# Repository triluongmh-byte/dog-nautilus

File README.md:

# Nautilus Dog V0

A phone-controlled, four-legged robot prototype with **one continuous-rotation micro servo per leg**. Each servo drives a pair of noncircular nautilus gears and a Jansen linkage to produce a walking foot path.

| Side view | Lid removed |
| --- | --- |
|  |  |

These images are renders of the project CAD, not photographs of a printed robot.

**Status: design and software prototype.** CAD checks and firmware builds have been reported, but no physical print, assembly, powered test, or successful walking test has been confirmed. The latest electrical component choices still need mechanical fit checks.

[Shopping list](#shopping-list) · [Assembly workflow](#assembly-workflow) · [Build from source](#build-from-source) · [Known limitations](#known-limitations-and-manual-checks)

## How it works

Each leg follows this chain:

```text
Continuous-rotation servo
        ↓
Nautilus gear pair — one input revolution per output revolution,
                    with a varying speed ratio during the cycle
        ↓
Crank → Jansen linkage → foot path with a near-flat stance section
```

The front legs reach forward and the rear legs reach backward, placing the feet near the four corners of the body. The linkages provide the foot motion mechanically; this is a single-actuator-per-leg mechanism.

Continuous-rotation servos control speed and direction, not absolute angle. Leg phase is calibrated by hand and estimated in firmware. There is no encoder feedback or active balance control.

| Item | Current design |
| --- | --- |
| Frame + lid | 126 × 75 × 31 mm |
| Expansion posts | Extend 6 mm above the lid |
| Swept CAD envelope | Approximately 152.1 × 144.6 × 69.6 mm, including moving legs |
| Actuators | 4 SG90/FS90R-class **continuous-rotation** micro servos |
| Controller | ESP32-C3 SuperMini |
| Display | 1.54-inch, 128 × 64 OLED, I2C variant |
| Battery / motor supply | 2S 18650 pack with charging/protection modules; regulated 5 V |
| Assembly | Hand-wired electronics on perfboard; printed structure and M2 linkage joints |

See the [original brief](prompts/original.md), [reference assets](prompts/assets/REFERENCES.md), and [mechanical changes from the draft](case/DEVIATIONS.md).

## Phone control

The firmware creates a local Wi-Fi access point and serves the controller at **http://192.168.4.1**. A cloud service or dedicated phone app is not required.

- On-screen joystick and eight direction buttons: forward/backward, pivots, and forward/backward arcs. Release the joystick or a held direction button to stop.
- Adjustable speed and trot/walk gait selection.
- One driving phone at a time, with a take-control action.
- OLED Wi-Fi information/QR codes, facial expressions, and an estimated battery percentage.
- Captive-portal support to help phones open the controller. If it does not appear, open the address above manually.
- A **Love** command: heart eyes and, from standstill, a programmed sequence of six left/right sways using short alternating pivots. The physical result is untested.
- A drive-command timeout and low-battery stop. Calibration actions have separate behavior; keep the feet clear during calibration.

The diagonal controls describe curved paths, not sideways walking. Calibration at **http://192.168.4.1/cal** sets neutral trim, direction, seconds per revolution, and phase zero, then saves them to NVS. Recalibrate if legs move while powered off or phase drifts.

Details: [firmware guide](firmware/README.md), [wiring](firmware/WIRING.md), and [configuration constants](firmware/include/config.h).

## Shopping list

Quantities below are for **one robot**, before optional spares. They follow [parts.json](parts.json), [the hardware definitions](case/hardware.json), and [the wiring plan](engineering/harness.md). Module dimensions and supplied servo hardware still need measurement.

The original builder already owns **8 continuous-rotation servos**: use 4 and keep 4 as spares. New builders need 4. Buy a few spare small fasteners if ordering individual sizes.

### Electronics and power

| Item | Quantity | What to buy / check |
| --- | --- | --- |
| Continuous-rotation micro servo | 4 | SG90/FS90R-class size, explicitly sold as continuous rotation. A standard 180° SG90 is unsuitable. [FS90R reference](https://www.pololu.com/product/2820); verify the actual body, horn, spline, and mounting holes with the test coupon. |
| ESP32-C3 SuperMini | 1 | An extra board is optional. Match the actual pin labels and dimensions to [pinout.md](engineering/pinout.md); ESP32-C3 boards are not all interchangeable. |
| 1.54-inch OLED | 1 | 128 × 64, SSD1309-class, **4-pin I2C configuration**. Check module size, hole pattern, pin order, voltage, and controller selection. Some boards ship in SPI mode. |
| 5 V buck-boost regulator | 1 | Current reference: [Pololu S13V30F5](https://www.pololu.com/product/4082). Approximately 22.9 × 22.9 mm; **does not fit the existing 22 × 17 mm holder**. Output capability depends on input voltage and temperature; verify it under the real load. |
| USB-C 2S Li-ion charger, CHG1a | 1 | 8.4 V charge target, with documented cell balancing and the required midpoint connection. **Exact module and fit are not validated**; verify its documentation and dimensions before purchasing. A 1S charger is unsuitable. |
| 2S protection board, CHG1b | 1 | Current reference: HX-2S-JH20-class board with B+/BM/B−/P+/P− connections. Confirm the actual board's continuous-current rating, pinout, and compatibility with the charger; the current design calls for at least 5 A continuous discharge. |
| Matched 18650 Li-ion cells | 2 | Same model/batch, 65 mm long, with a documented continuous-discharge rating of at least 5 A per cell. The cradle assumes cells without individual protection PCBs; **external 2S protection is required**. Longer protected cells may not fit. |
| Resettable fuse / PTC | 1 | Current wiring plan calls for a roughly 4 A hold-current class part; check temperature derating and the final power design. |
| Power switch | 1 | Nominal 7 mm mounting hole and at least 3 A DC rating; verify the actual switch and contact arrangement. |
| Fan | 1 | 30 × 30 × 10 mm, 5 V, two wires; four mounting holes on a 23 mm square. |
| Perfboard | 1 | 2.54 mm pitch, cut to approximately 22 × 52 mm; match the four mounting holes and the wiring diagram. |
| USB-C data cable | 1 | For firmware upload; a charge-only cable is insufficient. |

**The charger/protection combination is still a prototype selection, not a validated battery assembly.** Confirm the exact modules and charging/protection behavior before connecting cells. For battery tabs, use a suitable spot-welding service rather than soldering directly to cells.

The KiCad carrier is the schematic/layout reference. The intended physical build is hand-wired; do not order a PCB as a substitute for the separate servo power wiring.

### Small electrical parts and wiring

| Item | Quantity | Purpose / specification |
| --- | --- | --- |
| 4.7 kΩ resistor | 2 | I2C pull-ups; through-hole 1/4 W parts for perfboard |
| 100 kΩ resistor | 1 | Battery divider |
| 33 kΩ resistor | 1 | Battery divider |
| 10 kΩ resistor | 4 | Servo signal pull-downs |
| 100 nF ceramic capacitor | 3 | Decoupling/filtering |
| 1000 µF electrolytic capacitor | 1 | At least 10 V; nominal body 8 × 11.5 mm. Current reference: Rubycon 10PX1000MEFC8X11.5; verify size and lead pitch. |
| 100–220 µF electrolytic capacitor | 1 optional | At least 10 V; reserve for MCU supply troubleshooting described in [bring-up](engineering/bringup.md). |
| Schottky diode | 1 | 1N5817 through-hole substitute or SS14 as documented in [parts.json](parts.json) |
| 2.54 mm male header, 40-pin strip | 2 | Cut for the module/header connections |
| Single-pin female crimp housings + contacts | 10 | Four servo signal connections plus spares |
| Low-profile 2-, 4-, and 6-pin female housings + contacts | 2 of each | Power/fan, OLED, and expansion connections; check clearance below the OLED |
| AWG24 stranded wire | About 2 m each of red, black, and orange | Power, ground, and signals; follow the branch lengths in the wiring plan |
| Heat-shrink tubing | 1 assortment | Insulate joints and wire splices |
| Nickel strip / prepared cell tabs | About 20 cm, as needed | Have the battery connections prepared with suitable equipment |
| Cable ties | A small pack | Battery retention and strain relief |

**Servo power wiring:** servo red/brown leads go to the +5 V/GND splice at the regulator output. Only the signal lead goes to **pin 1 of J3–J6**; leave pins 2–3 unused. Keep a common ground. Follow [the full wiring table](engineering/harness.md), not wire colors alone.

### Mechanical parts and consumables

| Item | Quantity | Used for |
| --- | --- | --- |
| PETG filament, 1.75 mm | 1 spool | Current assumed print profile; a 1 kg spool is a purchase unit, not an estimate of material used |
| M2 × 18 mm screw | 4 | Leg joint C |
| M2 × 14 mm screw | 12 | Leg joints D, E, and F |
| M2 × 8 mm screw | 4 | Leg joint G |
| M2 × 10 mm screw | 4 | OLED mounting |
| M2 hex nut | 28 | 20 for the legs + 8 for the OLED, including its nut spacers |
| M2 self-tapping screw | 4 | Perfboard/carrier holder; current shopping reference is M2 × 5 mm. Check pilot depth before fitting; original assembly notes also mention approximately 4 mm. |
| M3 × 10 mm self-tapping screw, pan head | 4 | Lid |
| M3 × 4 mm heat-set insert, approximately 4.6 mm OD | 8 | Expansion deck; confirm fit with the lid coupon |
| M3 × 16 mm screw | 4 | Fan |
| M3 hex nut | 4 | Fan |
| Supplied servo/horn screws and horns | 1 set per servo | Reuse the hardware supplied with the servos; dimensions are unmeasured |
| CA/superglue | 1 small bottle | Holders and the specified fixed/locked interfaces; keep it out of rotating bores |
| Foam double-sided tape | 1 roll | Electronic module mounting; final placement still needs checking |

Printed pins, gears, links, holders, frame, and lid come from the CAD; they are not additional purchased shafts or bearings. The original layout contains **47 production pieces** plus **5 separate test coupons**. The newer regulator installation omits the old buck holder; the CAD/plate set has not yet been reconciled with that change.

Useful tools: a 3D printer, soldering iron and solder/flux, multimeter, calipers, wire stripper, crimping tool, small screwdrivers/hex keys, heat-set insert tool, and a current-limited bench supply for bring-up.

## Assembly workflow

1. **Print the test coupons first.** Check the servo seat, module openings, gear mesh, linkage joint, and lid against real purchased parts. Resolve fit problems before printing the full set.
2. **Print the production parts** using the actual printer/material profile. The existing profile assumes a Bambu A1, 0.4 mm nozzle, PETG, and 0.20 mm layers; this is not a confirmed profile for every printer.
3. **Assemble the mechanism** using [the case guide](case/README.md) and [hardware definitions](case/hardware.json). Check free rotation through a full cycle.
4. **Fit the electronics and wire the robot** using [the harness table](engineering/harness.md). Check module clearances with the lid in place.
5. **Follow the staged bring-up procedure** in [bringup.md](engineering/bringup.md), starting without the battery or servos.
6. **Upload and calibrate the firmware** using [the firmware guide](firmware/README.md). Lift the feet clear for calibration, then perform a controlled first walking test.

[PRINT.md](PRINT.md) contains the existing print/assembly checklist, and [BUY.md](BUY.md) contains the earlier shopping checklist. Some supporting documents and the original brief are in Vietnamese; the consolidated shopping list above is in English.

## Known limitations and manual checks

- **Latest power modules need a mechanical update.** The Pololu regulator does not fit the original buck holder. The documented temporary approach is foam-tape mounting, but final placement, electrical isolation, and lid clearance need checking. The added protection board's proposed location above the cells has not been validated in CAD.
- **Confirm every bought-part envelope.** Servo bodies/horns, module sizes, fan, cell tabs, and factory screws have not been measured. Use the test coupons. The cradle assumes 65 mm cells.
- **Keep the Q pivot free.** Insert the Q pin from inside the body and glue it into the rocker only; it must rotate in the frame bore. Check both the servo-seat and leg-joint coupons for the pin interfaces. See [deviation D8](case/DEVIATIONS.md#d8-q-pin-turns-with-the-rocker-inserted-from-inside-the-box).
- **Check connector and screw height.** Wires under the OLED must leave sideways; the selected maximum is 11.5 mm above the header base. The ESP32 seating target is 2.5 mm, not a tall female socket. Verify carrier screw penetration and real nut/insert fits.
- **Inspect the printed frame and cable routes.** Small corner-boss protrusions may need deburring. Keep wiring out of moving links and away from the OLED underside; do not assume the route over the cells is clear.
- **Calibrate and inspect the display on hardware.** Phase tracking is open-loop. The Wi-Fi/URL QR sequence, battery text, and calibration behavior still need a real device check. Calibration spin has its own five-second limit; it is not equivalent to the normal driving timeout.
- **Generated viewers and printer handoff remain unconfirmed.** Earlier automated UI checks lacked usable WebGL/window access. The print-team handoff also failed despite a parsed 3MF; no print job was sent. This is separate from generating files for manual inspection.
- **Electrical estimates require measurements.** The current budget assumes about 2.8 A at 5 V; actual servo stall current and regulator thermal performance may exceed that model. Battery percentage is an estimate, not a fuel-gauge measurement.

These checks retain the practical findings from the original independent reviews. A passed CAD, ERC/DRC, or compile check does not establish physical fit, battery behavior, or walking performance.

## Build from source

The repository contains authored sources and the selected README images. **STEP/STL/3MF, generated reports, viewer HTML, and firmware binaries are not committed.** The output paths listed below appear only after building; they are not prebuilt GitHub downloads.

The current build pipeline targets **macOS**. It expects:

| Stage | Tools |
| --- | --- |
| Board | Autonomous Circuit's KiCad toolchain, Python 3.10+ (3.12 recommended), KiCad 10 CLI and matching pcbnew runtime, zsh, rsync |
| Case | Board tools plus CadQuery, NumPy, Matplotlib, VTK, Node.js, and Bambu Studio 2.7 at the path expected by the scripts |
| Firmware | Arduino CLI, ESP32 core 2.0.14, U8g2 and WebSockets libraries, Node.js, and a C++ compiler; QR sources are included |

Install/configure the toolchain from [Autonomous Circuit](https://github.com/autonomous-ai/autonomous-circuit/tree/main/harness/kicad) first. A Harness app session can supply the environment variables, but the app itself is not required: the Python wrapper scripts in that repository can also be used from a terminal.

```sh
git clone https://github.com/triluongmh-byte/dog-nautilus.git
cd dog-nautilus

# Replace this with your actual Autonomous Circuit checkout.
export CIRCUIT_REPO="/absolute/path/to/autonomous-circuit"
export KICAD_HARNESS_PYTHON="$CIRCUIT_REPO/harness/kicad/toolchain/python"
export KICAD_CASE_PYTHON="$CIRCUIT_REPO/harness/kicad/toolchain/case-python"

# Choose only the stage(s) you need.
./build.sh board
./build.sh case
```

For firmware, point Arduino CLI at the directories where **your** ESP32 core and libraries are installed:

```sh
export ARDUINO_DIRECTORIES_DATA="/absolute/path/to/arduino-data"
export ARDUINO_DIRECTORIES_USER="/absolute/path/to/arduino-sketchbook"
./build.sh firmware
```

Run `./build.sh` without stage names to build everything. The case stage builds missing board inputs first. The pipeline reuses the existing PCB copper; it does not reroute the board. Missing dependencies or failed checks stop the build, and the script does not install dependencies, flash a device, operate a printer, or place orders.

| Generated output | Local path after building |
| --- | --- |
| STEP/STL files and parts manifest | `case/out/` |
| Full production print project | `case/print/production.3mf` |
| Separate test-coupon print project | `case/print/test-only.3mf` |
| Assembly overview | `case/overview.html` |
| Native board preview/report files | `boards/main.board.json`, `boards/main_review/` |
| Mechanical verification reports | `case/reports/` |
| Firmware binary | `build/firmware/arduino-build/sketch.ino.bin` |
| Rebuild summary | `build/release-proof.json` |

The older mechanical sweep covered 72 poses using the earlier component envelopes. The November 16 firmware/electrical revision reports a successful Arduino CLI build and native board checks, while explicitly leaving the case unchanged. Regenerate and read the relevant reports for the revision you intend to build; do not combine an old mechanical pass with new module dimensions.

## Repository map

| Path | Contents |
| --- | --- |
| [case/](case/) and [tools/case/](tools/case/) | Parametric CAD, linkage geometry, checks, assembly and print tooling |
| [firmware/](firmware/) | ESP32-C3 sources, web controller, display and calibration |
| [design/](design/) | KiCad schematic/layout and local libraries |
| [engineering/](engineering/) | Wiring, power, protection, source evidence and bring-up |
| [parts.json](parts.json) and [case/hardware.json](case/hardware.json) | Electrical reference parts and mechanical hardware |
| [PILOT_CONTRACT.json](PILOT_CONTRACT.json) | Original sealed design inputs |
| [prompts/](prompts/) | Original brief, current summary and reference assets |
| [case/PRINTED-INVENTORY.md](case/PRINTED-INVENTORY.md) | Confirmed physical print inventory |

When contributing, describe the source revision, actual parts/printer/material, measurements, and checks performed. Keep generated CAD, slicer projects, reports, and binaries out of source commits. Report real print/fit/walking results separately from software checks.

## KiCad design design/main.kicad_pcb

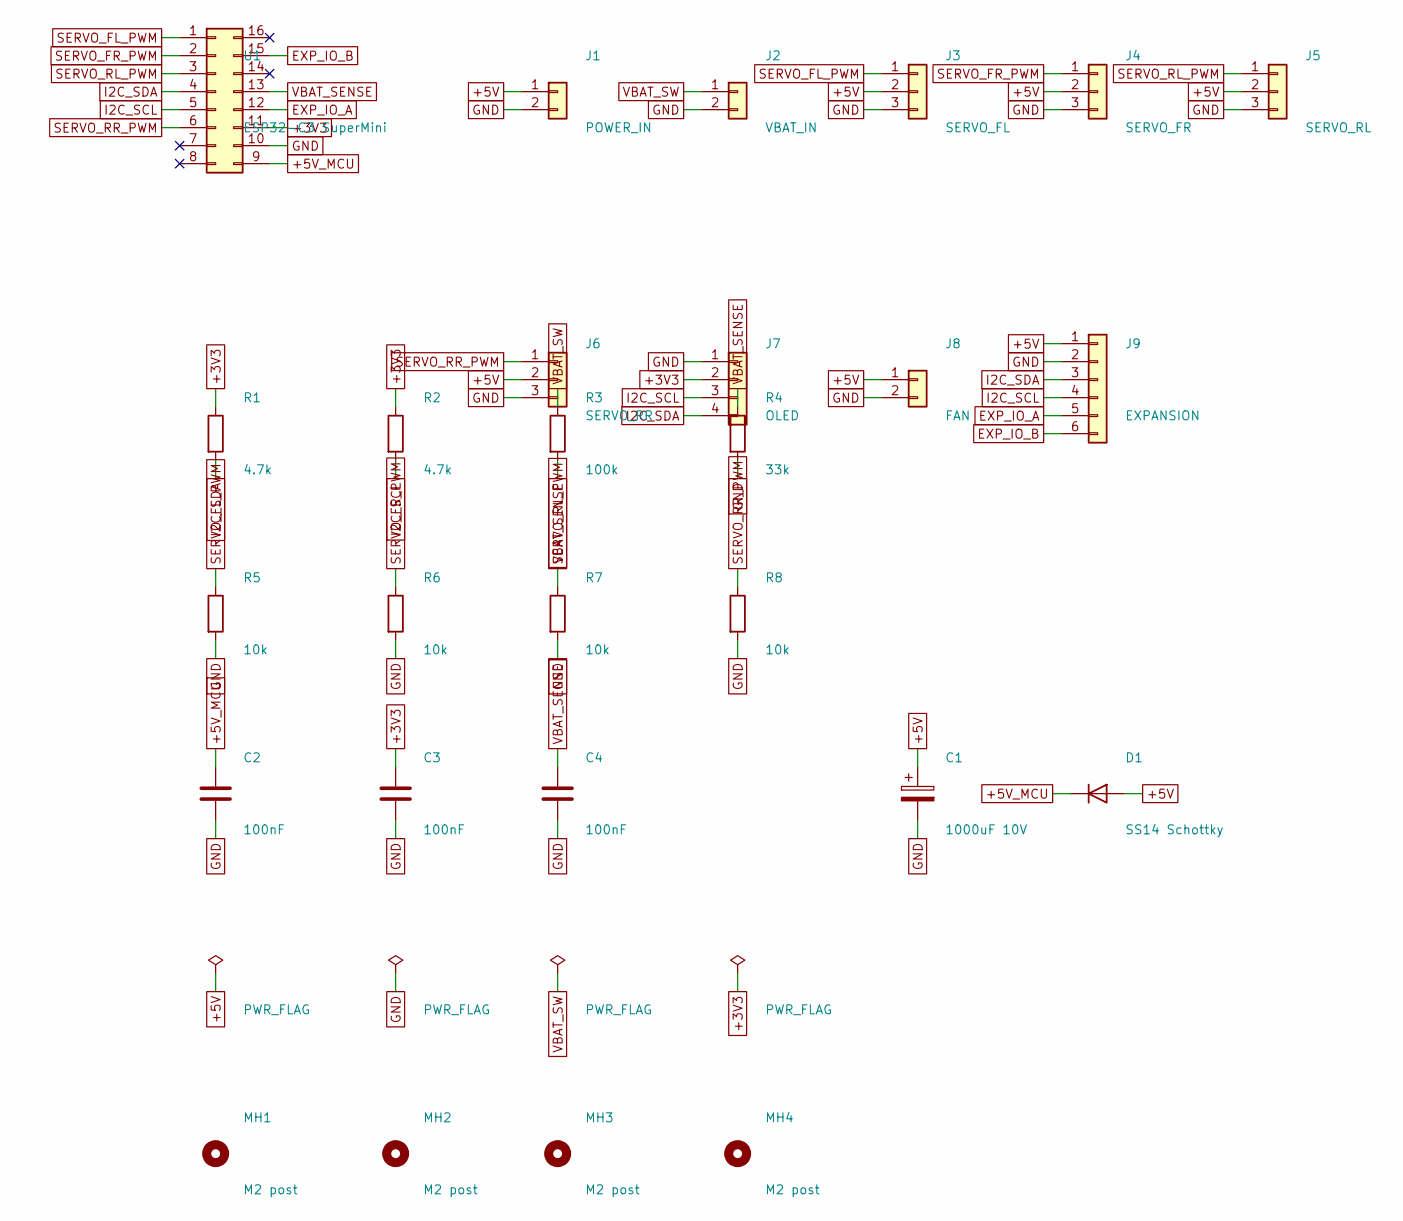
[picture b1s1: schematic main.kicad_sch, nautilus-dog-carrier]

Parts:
C1: 1000uF 10V; CP_Radial_D8.0mm_P3.50mm
C2, C3, C4: 100nF; C_0805_2012Metric
D1: SS14 Schottky; D_SMA
J1: POWER_IN; PinHeader_1x02_P2.54mm_Vertical
J2: VBAT_IN; PinHeader_1x02_P2.54mm_Vertical
J3: SERVO_FL; PinHeader_1x03_P2.54mm_Vertical
J4: SERVO_FR; PinHeader_1x03_P2.54mm_Vertical
J5: SERVO_RL; PinHeader_1x03_P2.54mm_Vertical
J6: SERVO_RR; PinHeader_1x03_P2.54mm_Vertical
J7: OLED; PinHeader_1x04_P2.54mm_Vertical
J8: FAN; PinHeader_1x02_P2.54mm_Vertical
J9: EXPANSION; PinHeader_1x06_P2.54mm_Vertical
MH1, MH2, MH3, MH4: M2 post; MountingHole_2.2mm_M2
R1, R2: 4.7k; R_0805_2012Metric
R3: 100k; R_0805_2012Metric
R4: 33k; R_0805_2012Metric
R5, R6, R7, R8: 10k; R_0805_2012Metric
U1: ESP32-C3 SuperMini; ESP32C3_SuperMini_2x8_P2.54

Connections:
+3V3: C3.1, J7.2, R1.1, R2.1, U1.11
+5V: C1.1, D1.2 (A), J1.1, J3.2, J4.2, J5.2, J6.2, J8.1, J9.1
+5V_MCU: C2.1, D1.1 (K), U1.9
EXP_IO_A: J9.5, U1.12
EXP_IO_B: J9.6, U1.15
GND: C1.2, C2.2, C3.2, C4.2, J1.2, J2.2, J3.3, J4.3, J5.3, J6.3, J7.1, J8.2, J9.2, R4.2, R5.2, R6.2, R7.2, R8.2, U1.10
I2C_SCL: J7.3, J9.4, R2.2, U1.5
I2C_SDA: J7.4, J9.3, R1.2, U1.4
SERVO_FL_PWM: J3.1, R5.1, U1.1
SERVO_FR_PWM: J4.1, R6.1, U1.2
SERVO_RL_PWM: J5.1, R7.1, U1.3
SERVO_RR_PWM: J6.1, R8.1, U1.6
VBAT_SENSE: C4.1, R3.2, R4.1, U1.13
VBAT_SW: J2.1, R3.1

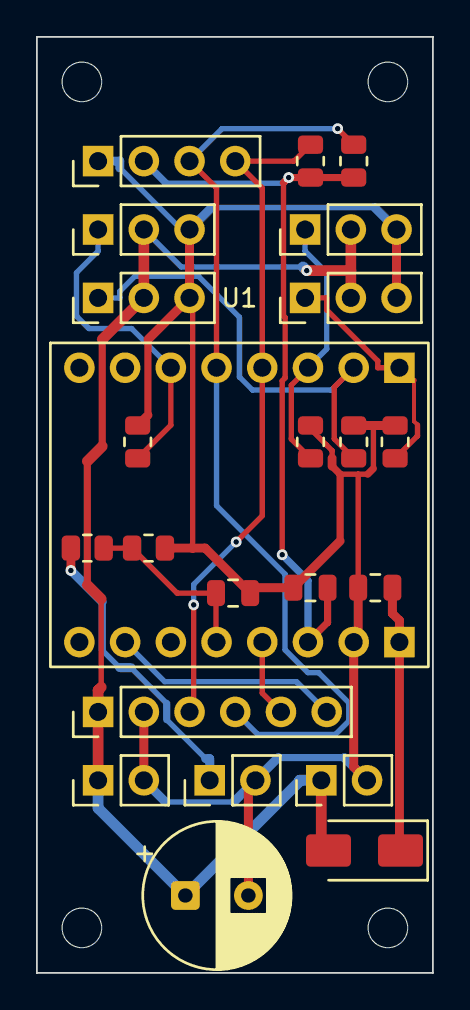
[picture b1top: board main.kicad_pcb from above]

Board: 2 copper layers, 22.0 x 52.0 mm, 27 parts (0 on the bottom side), 14 nets.

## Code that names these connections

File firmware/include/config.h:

// Pin map and tunables. Pins come only from PILOT_CONTRACT.json (interfaces.pins).
#pragma once
#include <stdint.h>

// ---- Pins (contract) ----
#define PIN_SERVO_FL 5
#define PIN_SERVO_FR 6
#define PIN_SERVO_RL 7
#define PIN_SERVO_RR 10
#define PIN_I2C_SDA 8   // shares the on-board LED: never drive it as GPIO
#define PIN_I2C_SCL 9
#define PIN_VBAT_SENSE 3  // ADC1_CH3
#define PIN_EXP_IO_A 4    // high-Z input at boot, firmware never drives
#define PIN_EXP_IO_B 1
// GPIO0/2/20/21 are no-connect: never touched.
#define I2C_FREQ_HZ 400000

// ---- Legs: index order FL, FR, RL, RR ----
enum Leg { LEG_FL = 0, LEG_FR, LEG_RL, LEG_RR, LEG_COUNT };
static const uint8_t SERVO_PINS[LEG_COUNT] = {PIN_SERVO_FL, PIN_SERVO_FR, PIN_SERVO_RL, PIN_SERVO_RR};
static const char* const LEG_NAMES[LEG_COUNT] = {"FL", "FR", "RL", "RR"};
static inline bool legIsLeft(int i) { return i == LEG_FL || i == LEG_RL; }

// ---- Servo pulses (us) ----
#define SERVO_FREQ_HZ 50
#define SERVO_PULSE_MIN_US 1000
#define SERVO_PULSE_MAX_US 2000
#define SERVO_NEUTRAL_DEFAULT_US 1500
#define SERVO_TRIM_LIMIT_US 150        // |trim| clamp
#define SERVO_FULL_SPEED_DELTA_US 400  // pulse offset from neutral at 100% command
#define SERVO_LEDC_BITS 14
// Left-side servos are mirrored: default direction sign +1 left, -1 right (calibrate!).
static const int8_t SERVO_SIGN_DEFAULT[LEG_COUNT] = {+1, -1, +1, -1};

// ---- Gait ----
#define DEFAULT_SEC_PER_REV 1.2f   // seconds per crank revolution at 100% command (calibrate)
#define GAIT_MIN_SPEED_PCT 20      // slider 0 stops; >0 maps to this..100 command
#define PHASE_KP 3.0f              // phase-error gain (rev/s per rev)
#define PHASE_CMD_TRIM_MAX 0.35f   // max correction added to command
#define GAIT_TICK_MS 10
#define TURN_INNER_SCALE 0.35f     // inner side speed factor in a diagonal (arc) move
#define JOY_DEADZONE 0.10f         // joystick: centre 10 % of each axis does nothing
#define JOY_SEND_MS 100            // page resends joystick / held button this often
#define WIGGLE_COUNT 6             // "love" emote: number of left-right sways
#define WIGGLE_HALF_MS 250         // each swing direction lasts this long (first/last are half)
#define WIGGLE_SPEED 0.45f         // pivot command during the sway, fraction of full speed
#define LOVE_FACE_HOLD_MS 2000     // heart-eyes face stays this long after the sway
#define PIVOT_SCALE 0.7f           // both sides at this fraction of the speed when spinning in place
#define NUDGE_MS 120               // calibration nudge pulse length
#define NUDGE_CMD 0.5f             // nudge command (fraction of full)

// ---- Safety ----
#define WATCHDOG_MS 1000  // stop if the driving phone sends no move command for this long
#define LOW_BATT_CUTOFF_V 6.6f
#define LOW_BATT_RESUME_V 6.9f
#define LOW_BATT_DEBOUNCE_MS 2000   // servo current sags VBAT; require sustained low

// ---- Battery ----
#define VBAT_DIVIDER_RATIO ((100.0f + 33.0f) / 33.0f)  // 100k top / 33k bottom (board target)
#define VBAT_OFFSET_V 0.0f
#define VBAT_EMPTY_V 6.4f
#define VBAT_FULL_V 8.4f
#define VBAT_SAMPLES 16

// ---- OLED ----
#define OLED_I2C_ADDR 0x3C        // 0x3D alternative; boot probes the other one if absent
#define OLED_I2C_ADDR_ALT 0x3D
#define OLED_USE_SSD1309 1        // 1 = SSD1309, 0 = SSD1306
#define OLED_ROTATION U8G2_R0     // U8G2_R0 / R1 / R2 / R3
#define QR_PHASE_MS 6000          // each QR page duration

// ---- Network ----
#define AP_SSID_PREFIX "NautilusDog-"
#define AP_CHANNEL 6
#define AP_MAX_CLIENTS 4
#define HTTP_PORT 80
#define WS_PORT 81
